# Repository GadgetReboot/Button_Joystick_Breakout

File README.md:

# Button_Joystick_Breakout
<br><br><BR><BR>
Thumb joystick and tactile buttons arranged in a D-pad for prototyping

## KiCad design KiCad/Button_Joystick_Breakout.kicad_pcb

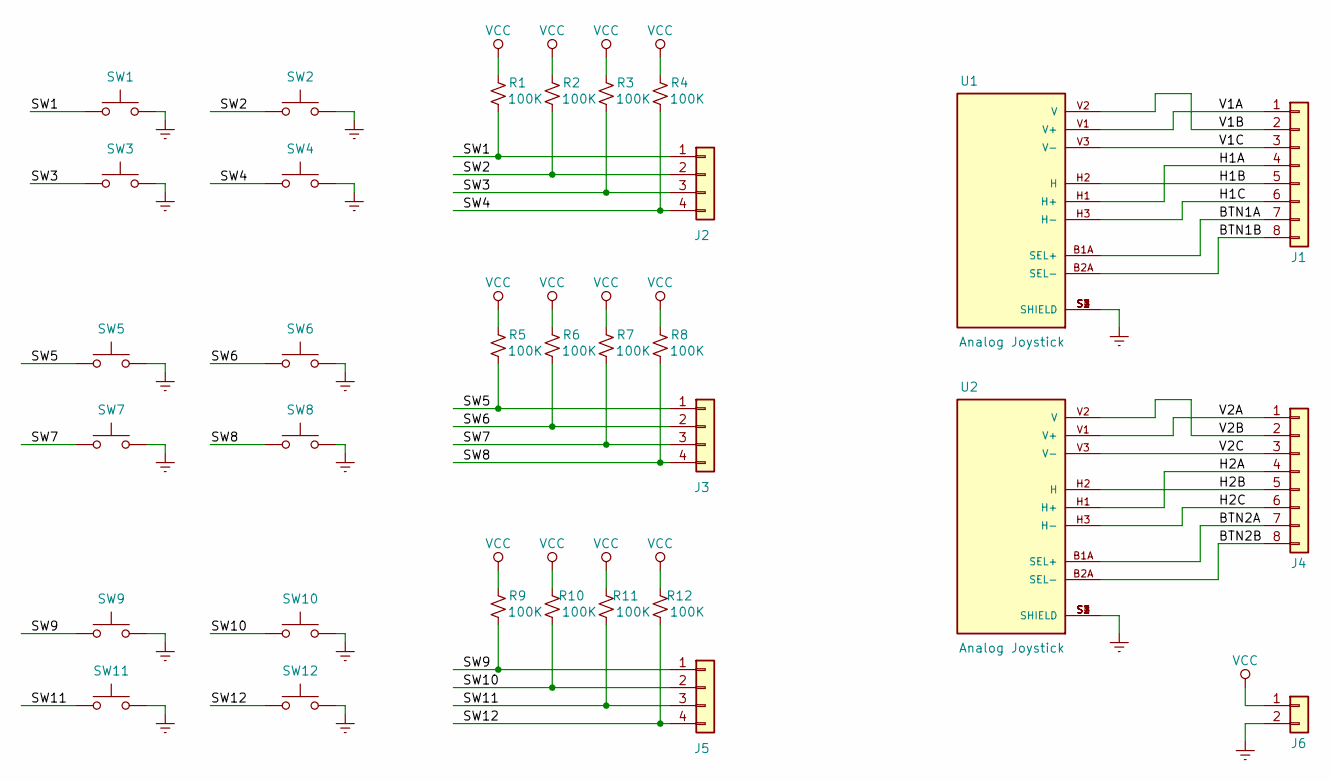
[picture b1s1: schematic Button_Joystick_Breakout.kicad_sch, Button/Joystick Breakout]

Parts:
J1, J4: Conn_01x08; PinHeader_1x08_P2.54mm_Vertical
J2, J3, J5: Conn_01x04; PinHeader_1x04_P2.54mm_Vertical
J6: Conn_01x02; PinHeader_1x02_P2.54mm_Vertical
R1, R2, R3, R4, R5, R6, R7, R8, R9, R10, R11, R12: 100K; R_0805_2012Metric_Pad1.20x1.40mm_HandSolder
SW1, SW2, SW3, SW4, SW5, SW6, SW7, SW8, SW9, SW10, SW11, SW12: SW_Push; SW_SPST_60x35
U1, U2: Analog Joystick; XDCR_COM-09032

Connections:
/BTN1A: J1.7, U1.B1A (SEL+)
/BTN1B: J1.8, U1.B2A (SEL-)
/BTN2A: J4.7, U2.B1A (SEL+)
/BTN2B: J4.8, U2.B2A (SEL-)
/H1A: J1.4, U1.H1 (H+)
/H1B: J1.5, U1.H2 (H)
/H1C: J1.6, U1.H3 (H-)
/H2A: J4.4, U2.H1 (H+)
/H2B: J4.5, U2.H2 (H)
/H2C: J4.6, U2.H3 (H-)
/SW1: J2.1, R1.2, SW1.1
/SW2: J2.2, R2.2, SW2.1
/SW3: J2.3, R3.2, SW3.1
/SW4: J2.4, R4.2, SW4.1
/SW5: J3.1, R5.2, SW5.1
/SW6: J3.2, R6.2, SW6.1
/SW7: J3.3, R7.2, SW7.1
/SW8: J3.4, R8.2, SW8.1
/SW9: J5.1, R9.2, SW9.1
/SW10: J5.2, R10.2, SW10.1
/SW11: J5.3, R11.2, SW11.1
/SW12: J5.4, R12.2, SW12.1
/V1A: J1.1, U1.V1 (V+)
/V1B: J1.2, U1.V2 (V)
/V1C: J1.3, U1.V3 (V-)
/V2A: J4.1, U2.V1 (V+)
/V2B: J4.2, U2.V2 (V)
/V2C: J4.3, U2.V3 (V-)
GNDREF: J6.2, SW1.2, SW2.2, SW3.2, SW4.2, SW5.2, SW6.2, SW7.2, SW8.2, SW9.2, SW10.2, SW11.2, SW12.2, U1.S1 (SHIELD), U1.S2 (SHIELD), U1.S3 (SHIELD), U1.S4 (SHIELD), U2.S1 (SHIELD), U2.S2 (SHIELD), U2.S3 (SHIELD), U2.S4 (SHIELD)
VCC: J6.1, R1.1, R2.1, R3.1, R4.1, R5.1, R6.1, R7.1, R8.1, R9.1, R10.1, R11.1, R12.1

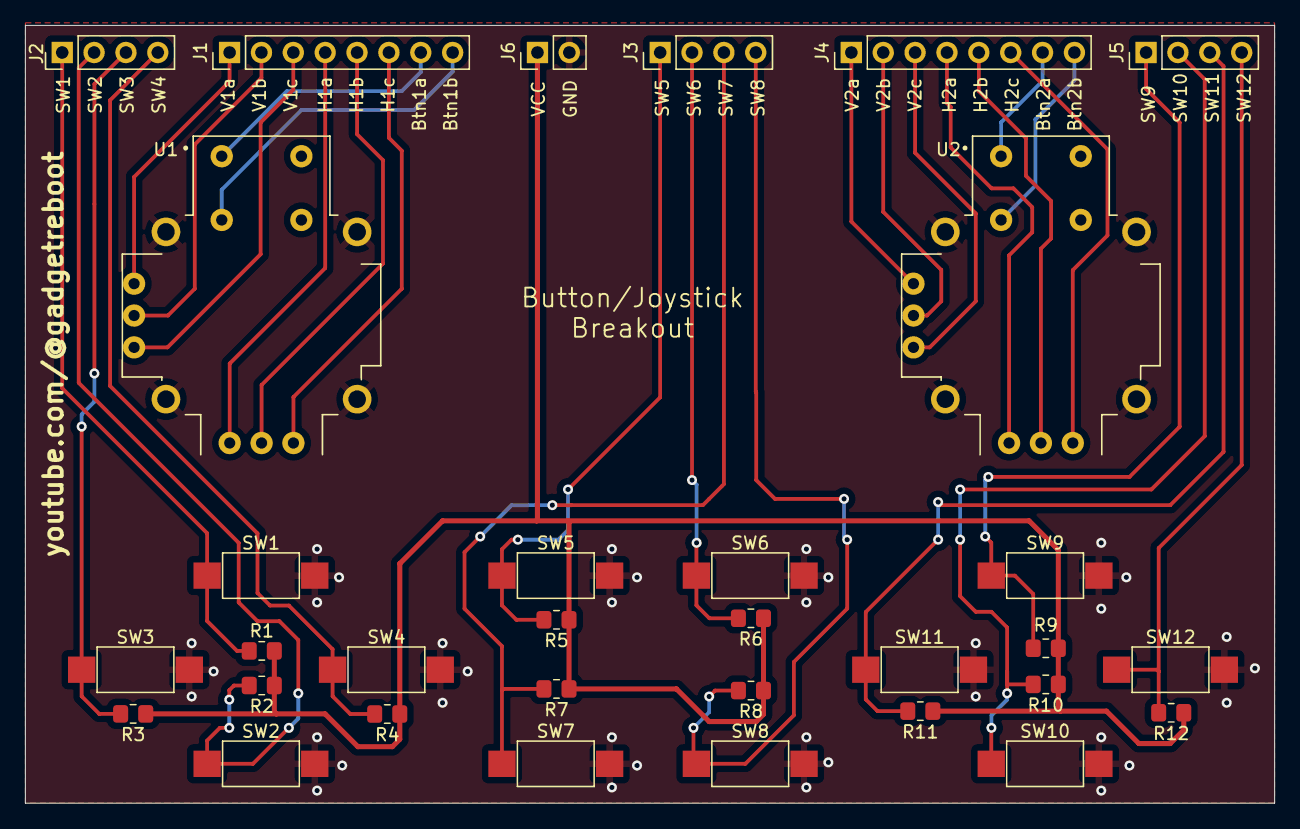
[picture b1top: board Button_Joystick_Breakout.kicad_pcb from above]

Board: 2 copper layers, 99.6 x 62.0 mm, 32 parts (0 on the bottom side), 30 nets.
